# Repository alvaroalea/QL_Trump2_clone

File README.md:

# SINCLAIR QL Trump Card V2 disk interface

(C) 2022 Alvaro Alea Fernandez

License under: CERN Open Hardware Licence Version 2 - Strongly Reciprocal

https://ohwr.org/cern_ohl_s_v2.txt

Available in the market in 4 ways, 0K, 256Kb/ACE, 512Kb, 768Kb and Treo (256Kb aditional).

Only 0Kb has been tested.

Check the readme in the GAL folder, up to now, I only be able to make it work without RAM.

# Technical Info

## Components to use

### 4040
We found that not all manufacturer made CD4040 or 74HC4040 in the same way, and some made counter with rise-edge of clock, and some with falling-edge.

The trump card need falling edge or will mess with the refresh cycle and do not work.

The eprom/gal programer TL-866 II+ has a function to test TLL chips, but fail to detect it and consider valid both variants.

We have include the file 4040-test.lgc with a custom test that when load on the programmer allow to detect valid 74HC4040 variants. (best to use 74HC4040 that CD4040)

### RAM Chips
Trump Card use 514256 Ram chips, this is 4bits x 256K (1Mbit) Dinamic RAM.

Trump Card use a special refresh mode of this chips called hidden refresh, but not all manufacturer implement in tha same way.

Has been reported that Texas Instrument TMS44C256 are not valid and will cause errors on boot.

Motorola (MCM514256) Siemens (HYB514256) and OKI (MSM514256) has been reported to work

Toshiba (TC514256) and GoldStart (GM71C4256) al also valid acording to datasheet, but not tested.

The trump card schematic used 0 wait state ram, even in the refresh cycle, and for that speed of the dram shall be between 70 and 100ns, 120ns or slower are not valid.

HOLD

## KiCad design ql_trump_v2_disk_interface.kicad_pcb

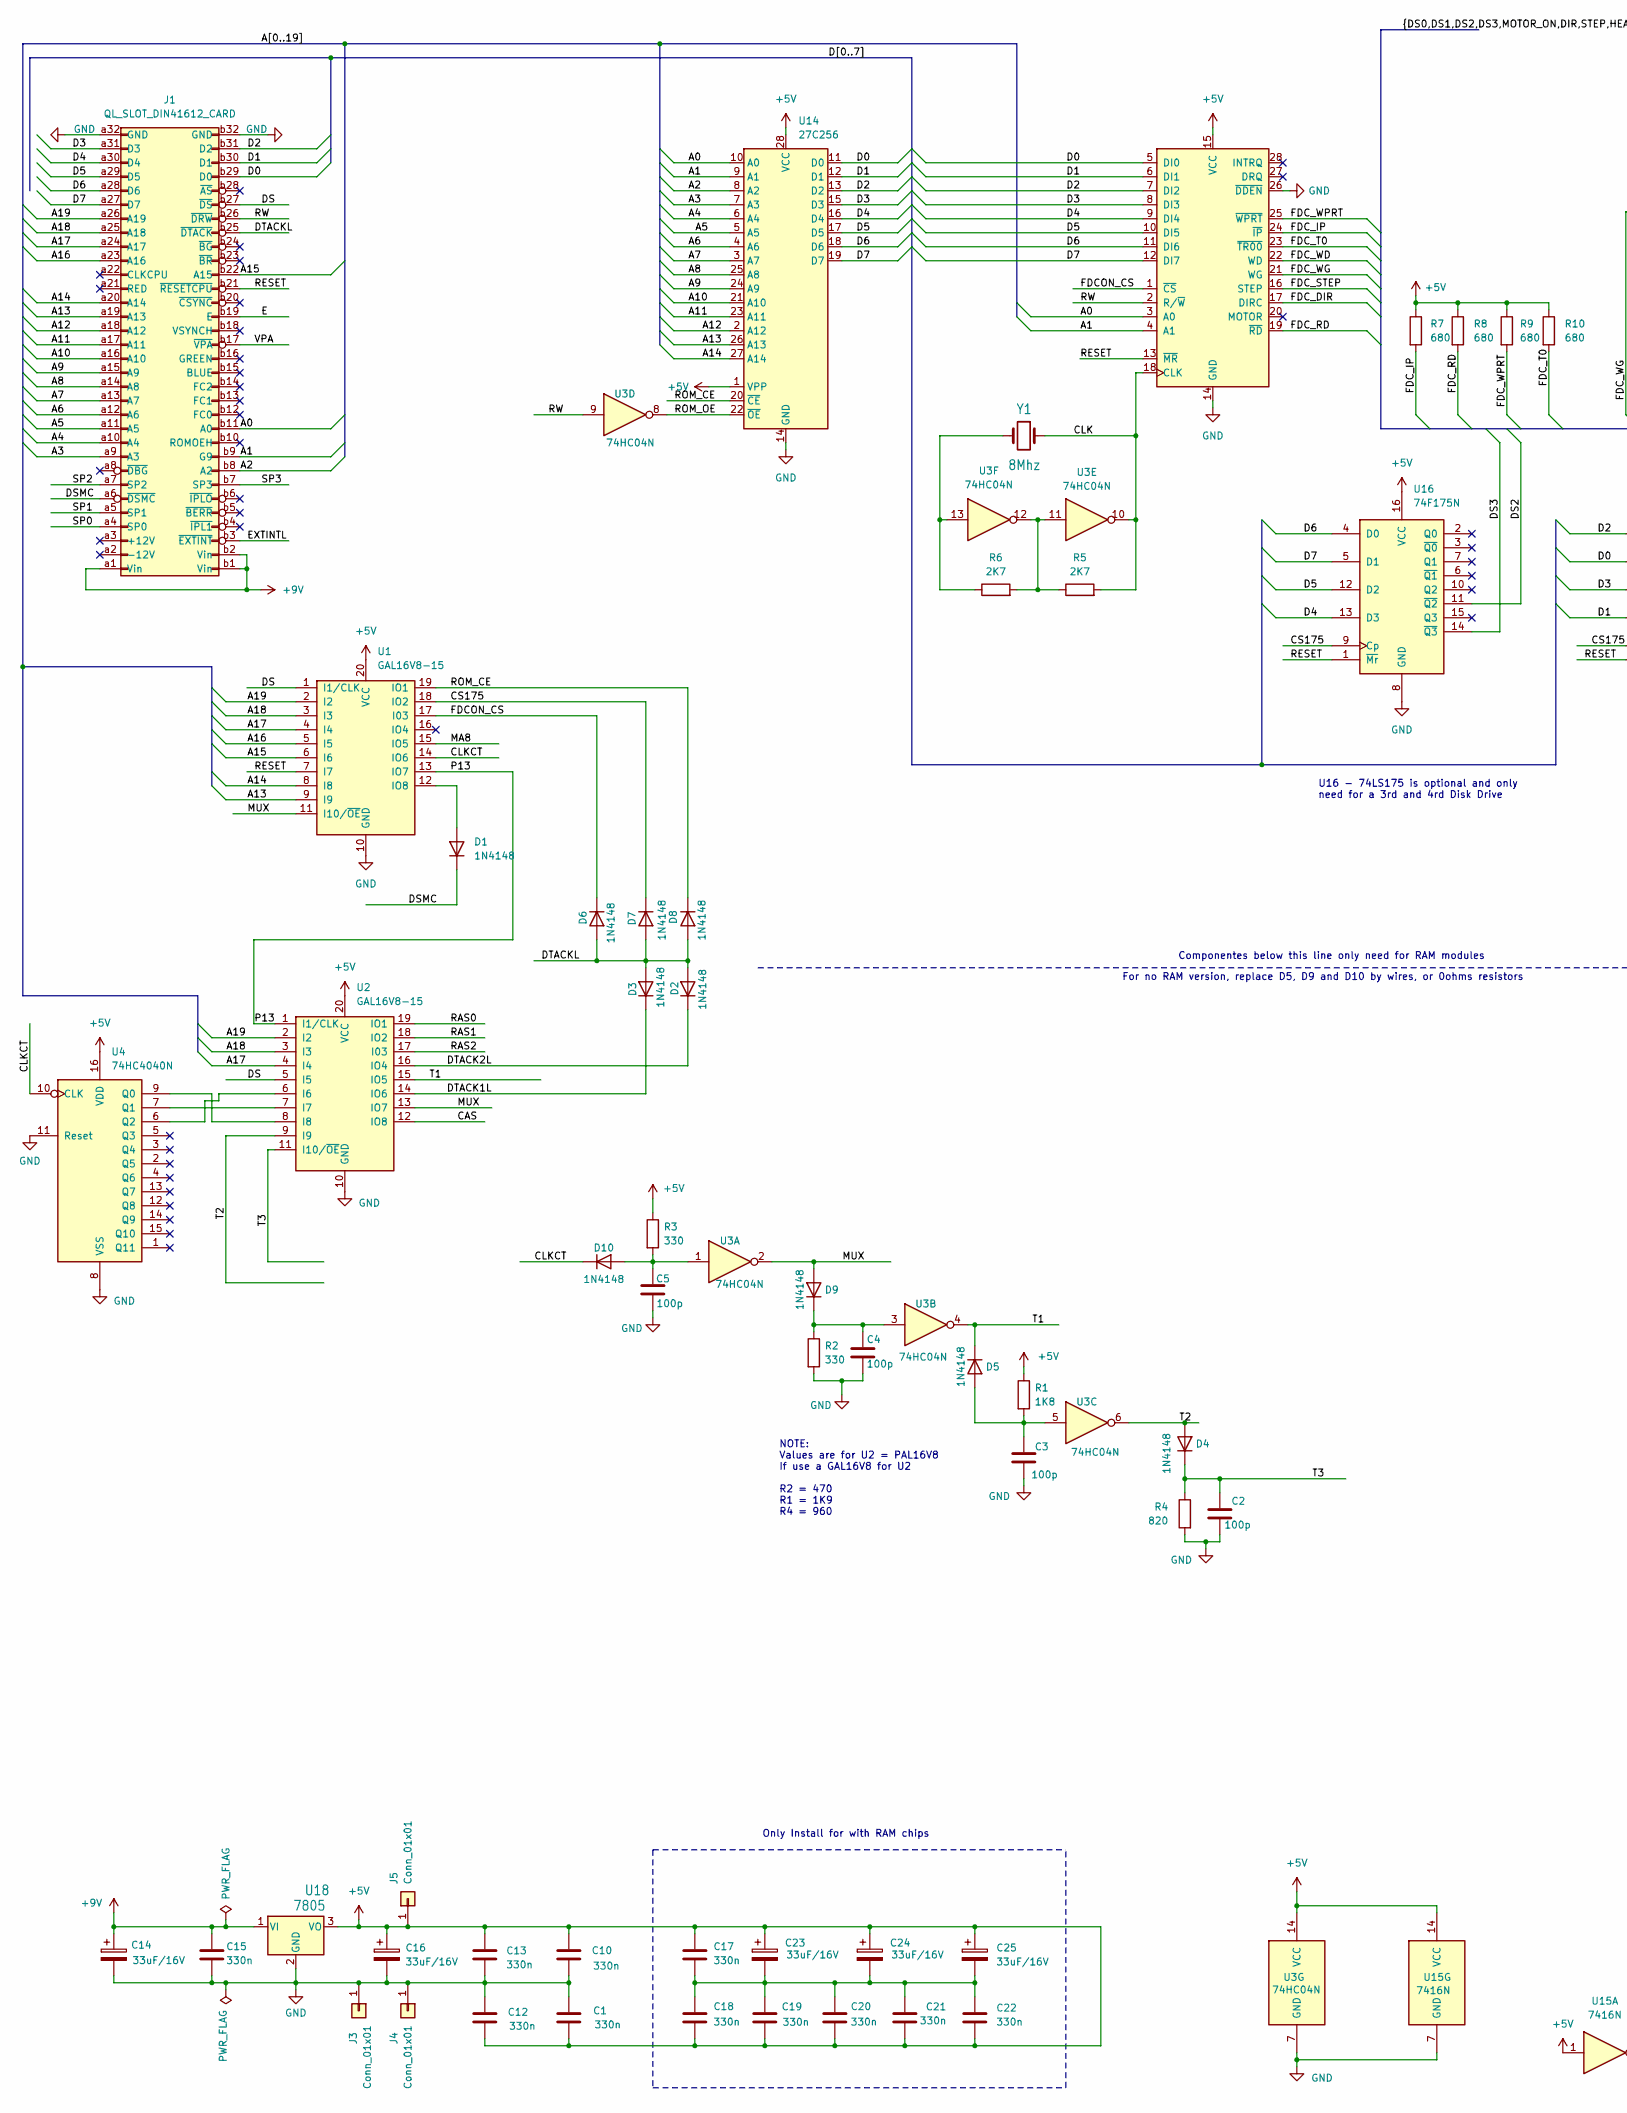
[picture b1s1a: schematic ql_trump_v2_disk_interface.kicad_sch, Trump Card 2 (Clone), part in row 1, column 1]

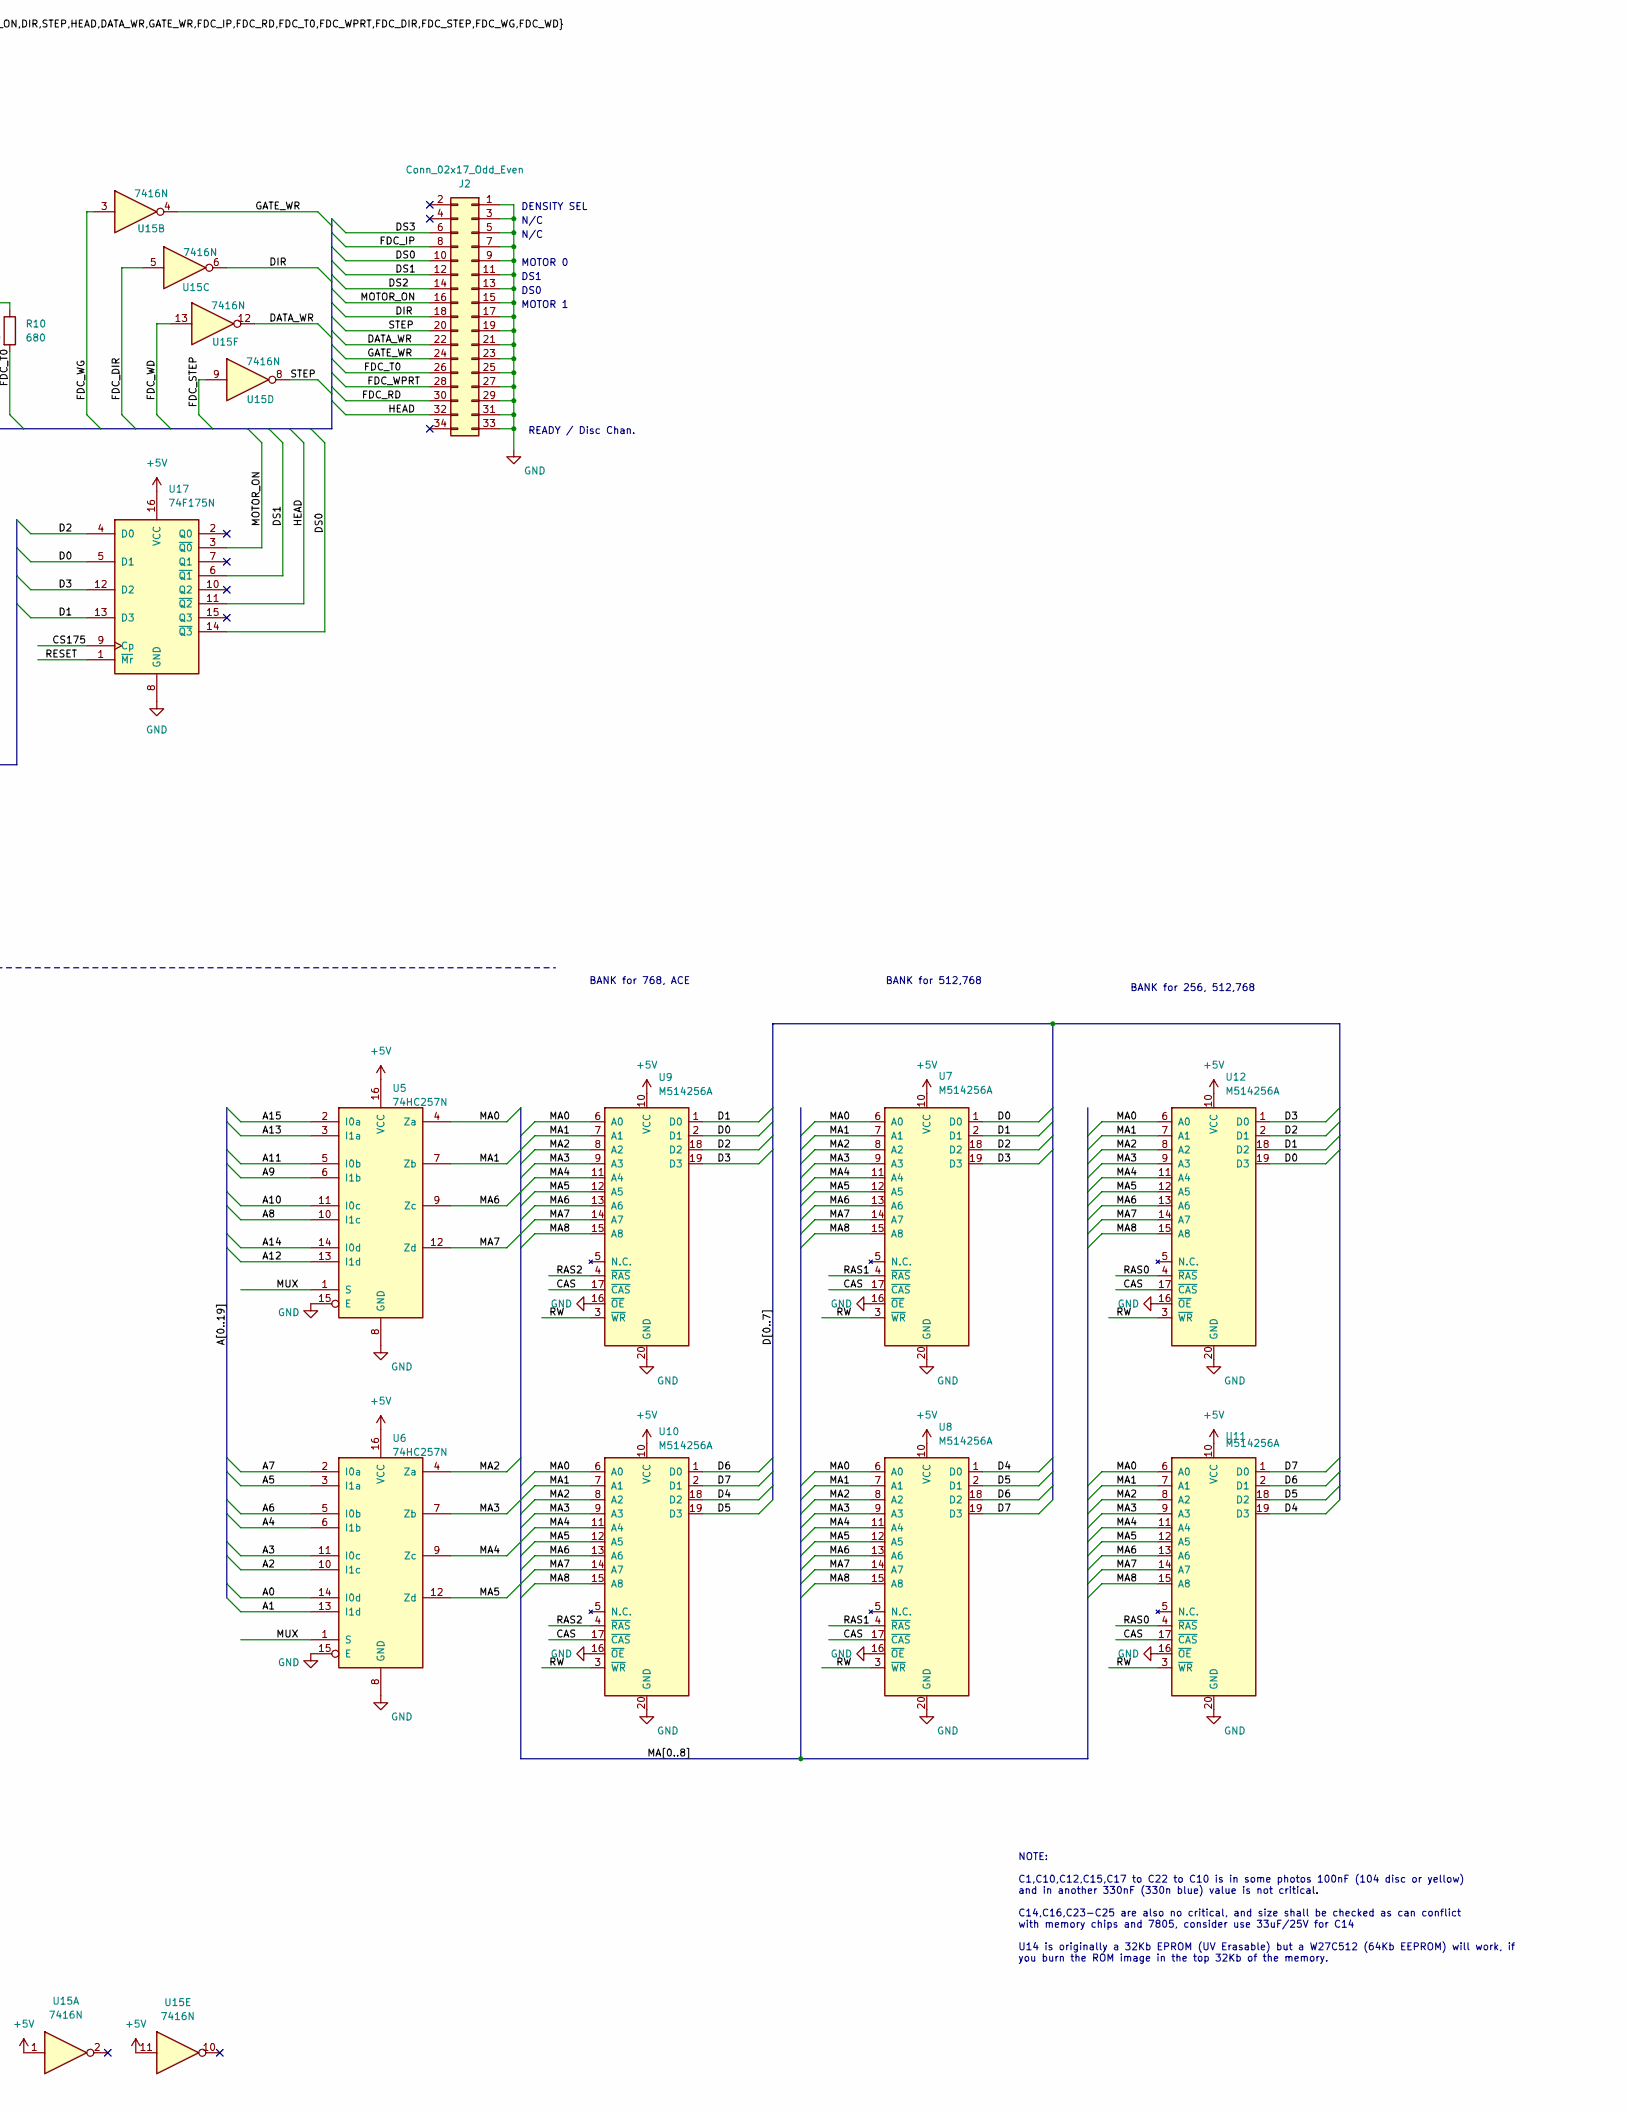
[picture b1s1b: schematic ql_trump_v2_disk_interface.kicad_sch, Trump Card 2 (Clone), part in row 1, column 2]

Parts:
C1, C10, C12, C17, C18, C19, C20, C21, C22: 330n; C_Disc_D7.5mm_W4.4mm_P5.00mm
C2, C3, C4, C5: 100p; C_Disc_D7.0mm_W2.5mm_P5.00mm
C13, C15: 330n; C_Disc_D5.1mm_W3.2mm_P5.00mm
C14, C16, C23, C24, C25: 33uF/16V; CP_Axial_L11.0mm_D5.0mm_P18.00mm_Horizontal
D1, D2, D3, D4, D5, D6, D7, D8, D9, D10: 1N4148; D_DO-35_SOD27_P10.16mm_Horizontal
J1: QL_SLOT_DIN41612_CARD; DIN41612_Q_2x32_Female_Horizontal_THT
J2: Conn_02x17_Odd_Even; PinHeader_2x17_P2.54mm_Horizontal
J3, J4, J5: Conn_01x01; TestPoint_THTPad_D1.5mm_Drill0.7mm
R1: 1K8; R_Axial_DIN0207_L6.3mm_D2.5mm_P10.16mm_Horizontal
R2, R3: 330; R_Axial_DIN0207_L6.3mm_D2.5mm_P10.16mm_Horizontal
R4: 820; R_Axial_DIN0207_L6.3mm_D2.5mm_P10.16mm_Horizontal
R5, R6: 2K7; R_Axial_DIN0207_L6.3mm_D2.5mm_P10.16mm_Horizontal
R7, R8, R9, R10: 680; R_Axial_DIN0207_L6.3mm_D2.5mm_P10.16mm_Horizontal
U1, U2: GAL16V8-15; DIP-20_W7.62mm
U3: 74HC04N; DIP-14_W7.62mm
U4: 74HC4040N; DIP-16_W7.62mm
U5, U6: 74HC257N; DIP-16_W7.62mm
U7, U8, U9, U10, U11, U12: M514256A; DIP-20_W7.62mm
U13: FDC_WD1772; DIP-28_W15.24mm
U14: 27C256; DIP-28_W15.24mm
U15: 7416N; DIP-14_W7.62mm
U16, U17: 74F175N; DIP-16_W7.62mm
U18: 7805; TO-220-3_Horizontal_TabDown
Y1: 8Mhz; Crystal_HC18-U_Vertical

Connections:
+5V: C1.1, C10.2, C12.1, C13.1, C16.1, C17.1, C18.1, C19.2, C20.1, C21.2, C22.1, C23.1, C24.1, C25.1, J5.1, R1.1, R3.1, R7.1, R8.1, R9.1, R10.1, U1.20 (VCC), U2.20 (VCC), U3.14 (VCC), U4.16 (VDD), U5.16 (VCC), U6.16 (VCC), U7.10 (VCC), U8.10 (VCC), U9.10 (VCC), U10.10 (VCC), U11.10 (VCC), U12.10 (VCC), U13.15 (VCC), U14.1 (VPP), U14.28 (VCC), U15.1, U15.11, U15.14 (VCC), U16.16 (VCC), U17.16 (VCC), U18.3 (VO)
+9V: C14.1, C15.1, J1.a1 (Vin), J1.b1 (Vin), J1.b2 (Vin), U18.1 (VI)
/A0: J1.b11 (A0), U6.14 (I0d), U13.3 (A0), U14.10 (A0)
/A1: J1.b9 (G9), U6.13 (I1d), U13.4 (A1), U14.9 (A1)
/A2: J1.b8 (A2), U6.10 (I1c), U14.8 (A2)
/A3: J1.a9 (A3), U6.11 (I0c), U14.7 (A3)
/A4: J1.a10 (A4), U6.6 (I1b), U14.6 (A4)
/A5: J1.a11 (A5), U6.3 (I1a), U14.5 (A5)
/A6: J1.a12 (A6), U6.5 (I0b), U14.4 (A6)
/A7: J1.a13 (A7), U6.2 (I0a), U14.3 (A7)
/A8: J1.a14 (A8), U5.10 (I1c), U14.25 (A8)
/A9: J1.a15 (A9), U5.6 (I1b), U14.24 (A9)
/A10: J1.a16 (A10), U5.11 (I0c), U14.21 (A10)
/A11: J1.a17 (A11), U5.5 (I0b), U14.23 (A11)
/A12: J1.a18 (A12), U5.13 (I1d), U14.2 (A12)
/A13: J1.a19 (A13), U1.9 (I9), U5.3 (I1a), U14.26 (A13)
/A14: J1.a20 (A14), U1.8 (I8), U5.14 (I0d), U14.27 (A14)
/A15: J1.b22 (A15), U1.6 (I6), U5.2 (I0a)
/A16: J1.a23 (A16), U1.5 (I5)
/A17: J1.a24 (A17), U1.4 (I4), U2.4 (I4)
/A18: J1.a25 (A18), U1.3 (I3), U2.3 (I3)
/A19: J1.a26 (A19), U1.2 (I2), U2.2 (I2)
/CAS: U2.12 (IO8), U7.17 (~CAS), U8.17 (~CAS), U9.17 (~CAS), U10.17 (~CAS), U11.17 (~CAS), U12.17 (~CAS)
/CLK: R5.2, U3.10, U13.18 (CLK), Y1.1
/CLKCT: D10.1 (K), U1.14 (IO6), U4.10 (CLK)
/CS175: D7.1 (K), U1.18 (IO2), U16.9 (Cp), U17.9 (Cp)
/D0: J1.b29 (D0), U7.1 (D0), U9.2 (D1), U12.19 (D3), U13.5 (DI0), U14.11 (D0), U17.5 (D1)
/D1: J1.b30 (D1), U7.2 (D1), U9.1 (D0), U12.18 (D2), U13.6 (DI1), U14.12 (D1), U17.13 (D3)
/D2: J1.b31 (D2), U7.18 (D2), U9.18 (D2), U12.2 (D1), U13.7 (DI2), U14.13 (D2), U17.4 (D0)
/D3: J1.a31 (D3), U7.19 (D3), U9.19 (D3), U12.1 (D0), U13.8 (DI3), U14.15 (D3), U17.12 (D2)
/D4: J1.a30 (D4), U8.1 (D0), U10.18 (D2), U11.19 (D3), U13.9 (DI4), U14.16 (D4), U16.13 (D3)
/D5: J1.a29 (D5), U8.2 (D1), U10.19 (D3), U11.18 (D2), U13.10 (DI5), U14.17 (D5), U16.12 (D2)
/D6: J1.a28 (D6), U8.18 (D2), U10.1 (D0), U11.2 (D1), U13.11 (DI6), U14.18 (D6), U16.4 (D0)
/D7: J1.a27 (D7), U8.19 (D3), U10.2 (D1), U11.1 (D0), U13.12 (DI7), U14.19 (D7), U16.5 (D1)
/DATA_WR: J2.22, U15.12
/DIR: J2.18, U15.6
/DS: J1.b27 (~DS), U1.1 (I1/CLK), U2.5 (I5)
/DS0: J2.10, U17.14 (~Q3)
/DS1: J2.12, U17.6 (~Q1)
/DS2: J2.14, U16.11 (~Q2)
/DS3: J2.6, U16.14 (~Q3)
/DSMC: D1.1 (K), J1.a6 (~DSMC)
/DTACK1L: D3.1 (K), U2.14 (IO6)
/DTACK2L: D2.1 (K), U2.16 (IO4)
/DTACKL: D2.2 (A), D3.2 (A), D6.2 (A), D7.2 (A), D8.2 (A), J1.b25 (~DTACK)
/E: J1.b19 (E)
/EXTINTL: J1.b3 (~EXTINT)
/FDCON_CS: D6.1 (K), U1.17 (I03), U13.1 (~CS)
/FDC_DIR: U13.17 (DIRC), U15.5
/FDC_IP: J2.8, R7.2, U13.24 (~IP)
/FDC_RD: J2.30, R8.2, U13.19 (~RD)
/FDC_STEP: U13.16 (STEP), U15.9
/FDC_T0: J2.26, R10.2, U13.23 (~TR00)
/FDC_WD: U13.22 (WD), U15.13
/FDC_WG: U13.21 (WG), U15.3
/FDC_WPRT: J2.28, R9.2, U13.25 (~WPRT)
/GATE_WR: J2.24, U15.4
/HEAD: J2.32, U17.11 (~Q2)
/MA0: U5.4 (Za), U7.6 (A0), U8.6 (A0), U9.6 (A0), U10.6 (A0), U11.6 (A0), U12.6 (A0)
/MA1: U5.7 (Zb), U7.7 (A1), U8.7 (A1), U9.7 (A1), U10.7 (A1), U11.7 (A1), U12.7 (A1)
/MA2: U6.4 (Za), U7.8 (A2), U8.8 (A2), U9.8 (A2), U10.8 (A2), U11.8 (A2), U12.8 (A2)
/MA3: U6.7 (Zb), U7.9 (A3), U8.9 (A3), U9.9 (A3), U10.9 (A3), U11.9 (A3), U12.9 (A3)
/MA4: U6.9 (Zc), U7.11 (A4), U8.11 (A4), U9.11 (A4), U10.11 (A4), U11.11 (A4), U12.11 (A4)
/MA5: U6.12 (Zd), U7.12 (A5), U8.12 (A5), U9.12 (A5), U10.12 (A5), U11.12 (A5), U12.12 (A5)
/MA6: U5.9 (Zc), U7.13 (A6), U8.13 (A6), U9.13 (A6), U10.13 (A6), U11.13 (A6), U12.13 (A6)
/MA7: U5.12 (Zd), U7.14 (A7), U8.14 (A7), U9.14 (A7), U10.14 (A7), U11.14 (A7), U12.14 (A7)
/MA8: U1.15 (IO5), U7.15 (A8), U8.15 (A8), U9.15 (A8), U10.15 (A8), U11.15 (A8), U12.15 (A8)
/MOTOR_ON: J2.16, U17.3 (~Q0)
/MUX: D9.2 (A), U1.11 (I10/~OE), U2.13 (IO7), U3.2, U5.1 (S), U6.1 (S)
/P13: U1.13 (IO7), U2.1 (I1/CLK)
/RAS0: U2.19 (IO1), U11.4 (~RAS), U12.4 (~RAS)
/RAS1: U2.18 (IO2), U7.4 (~RAS), U8.4 (~RAS)
/RAS2: U2.17 (I03), U9.4 (~RAS), U10.4 (~RAS)
/RESET: J1.b21 (~RESETCPU), U1.7 (I7), U13.13 (~MR), U16.1 (~Mr), U17.1 (~Mr)
/ROM_CE: D8.1 (K), U1.19 (IO1), U14.20 (~CE)
/ROM_OE: U3.8, U14.22 (~OE)
/RW: J1.b26 (~DRW), U3.9, U7.3 (~WR), U8.3 (~WR), U9.3 (~WR), U10.3 (~WR), U11.3 (~WR), U12.3 (~WR), U13.2 (R/~W)
/SP0: J1.a4 (SP0)
/SP1: J1.a5 (SP1)
/SP2: J1.a7 (SP2)
/SP3: J1.b7 (SP3)
/STEP: J2.20, U15.8
/T1: D5.1 (K), U2.15 (IO5), U3.4
/T2: D4.2 (A), U2.9 (I9), U3.6
/T3: C2.2, D4.1 (K), R4.1, U2.11 (I10/~OE)
/VPA: J1.b17 (~VPA)
unnamed: D1.2 (A), U1.12 (IO8)
unnamed: C3.1, D5.2 (A), R1.2, U3.5
unnamed: C4.2, D9.1 (K), R2.1, U3.3
unnamed: C5.1, D10.2 (A), R3.2, U3.1
unnamed: R5.1, R6.2, U3.11, U3.12
unnamed: R6.1, U3.13, Y1.2
unnamed: U2.6 (I6), U4.6 (Q2)
unnamed: U2.7 (I7), U4.7 (Q1)
unnamed: U2.8 (I8), U4.9 (Q0)

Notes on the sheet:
NOTE: C1,C10,C12,C15,C17 to C22 to C10 is in some photos 100nF (104 disc or yellow) and in another 330nF (330n blue) value is not critical. C14,C16,C23-C25 are also no critical, and size shall be checked as can conflict with memory chips and 7805, consider use 33uF/25V for C14 U14 is originally a 3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
MOTOR 0
BANK for 512,768
DS0
DS1
READY / Disc Chan.
MOTOR 1
U16 - 74LS175 is optional and only need for a 3rd and 4rd Disk Drive
For no RAM version, replace D5, D9 and D10 by wires, or 0ohms resistors
Componentes below this line only need for RAM modules
N/C
Only Install for with RAM chips
BANK for 768, ACE
NOTE: Values are for U2 = PAL16V8 If use a GAL16V8 for U2 R2 = 470 R1 = 1K9 R4 = 960
DENSITY SEL
BANK for 256, 512,768

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
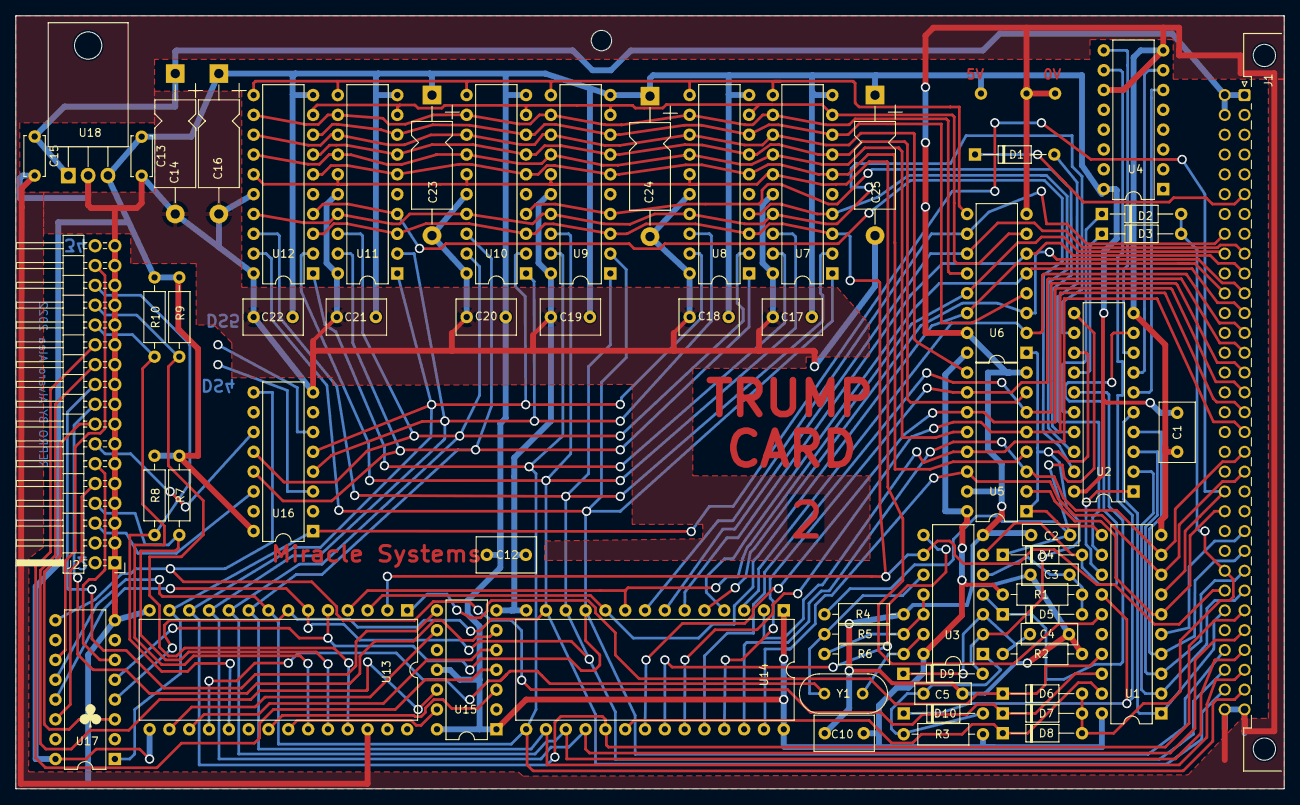
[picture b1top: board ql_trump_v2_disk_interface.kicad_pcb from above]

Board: 2 copper layers, 162.6 x 99.1 mm, 64 parts (0 on the bottom side), 89 nets.

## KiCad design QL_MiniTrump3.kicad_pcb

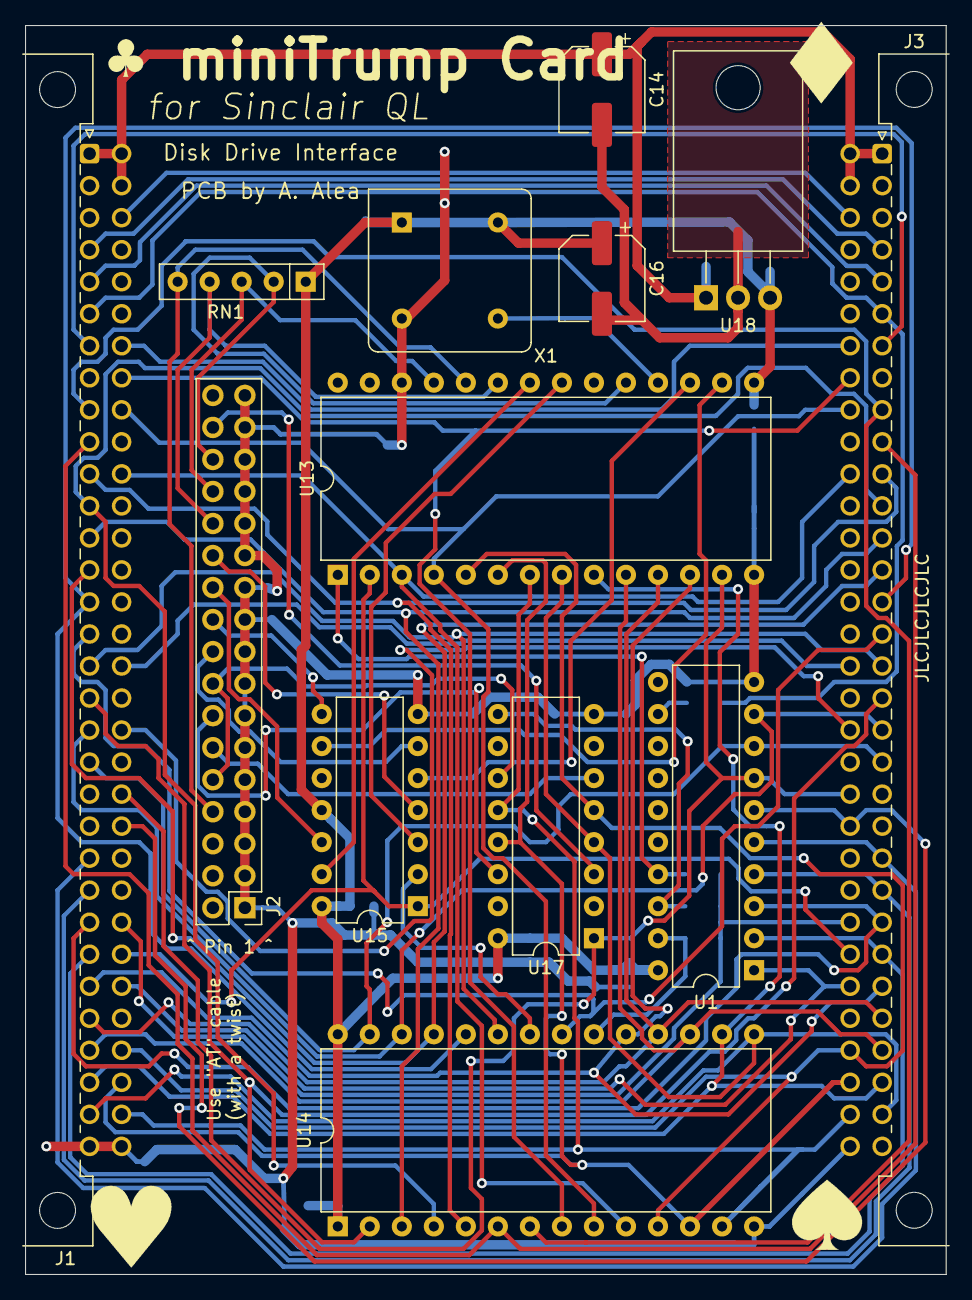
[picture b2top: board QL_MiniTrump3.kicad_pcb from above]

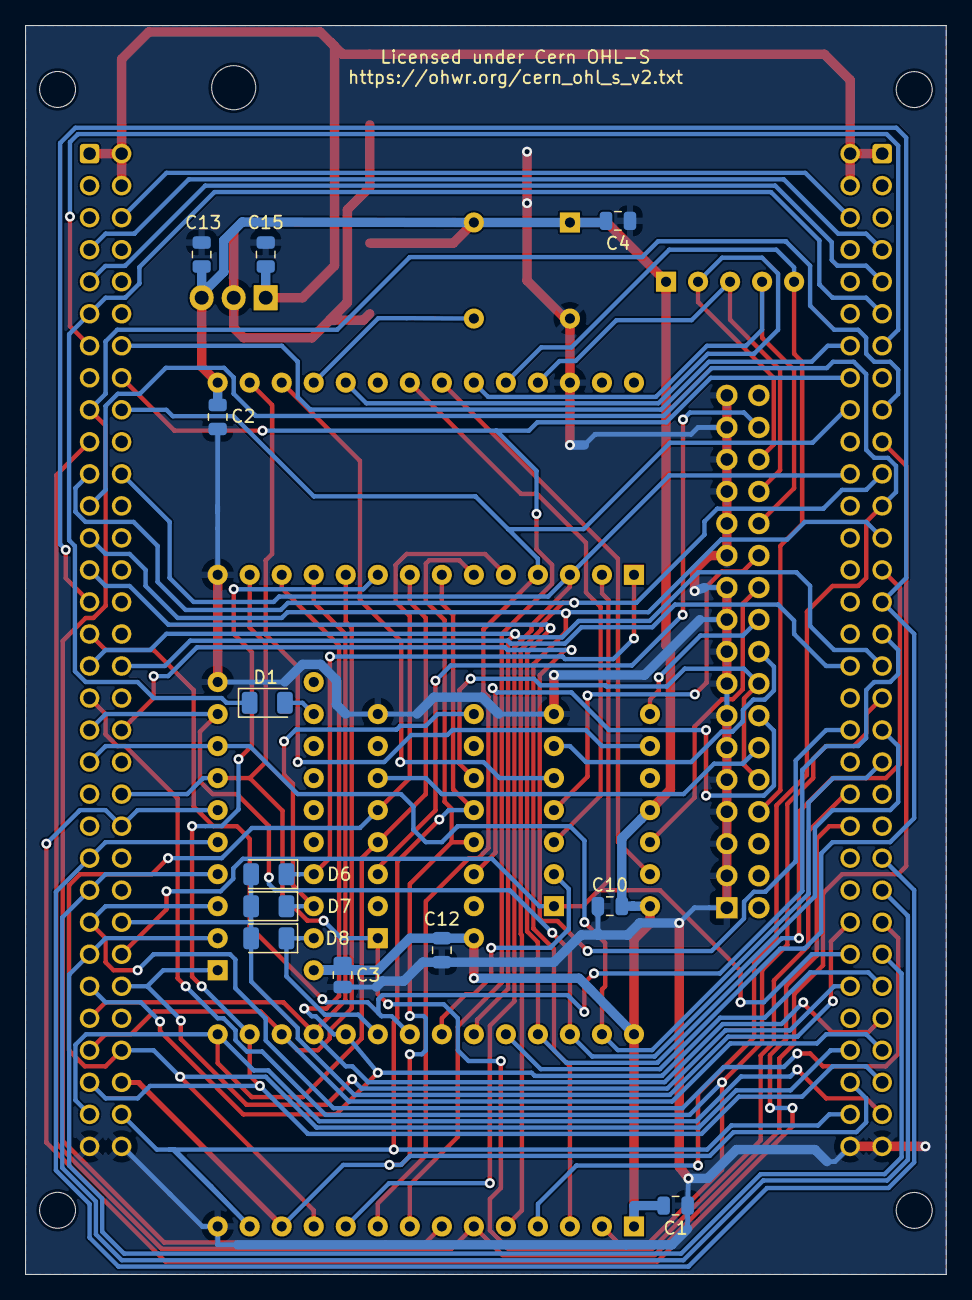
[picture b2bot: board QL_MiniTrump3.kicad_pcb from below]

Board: 2 copper layers, 73.0 x 99.1 mm, 25 parts (12 on the bottom side), 65 nets.

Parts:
C1, C2, C3, C4, C10, C12, C13, C15: C; C_0805_2012Metric
C14, C16: C_Polarized; CP_Elec_6.3x5.4
D1, D6, D7, D8: 1N4148; D_1206_3216Metric
J1: QL_SLOT_DIN41612_CARD; DIN41612_B_2x32_Female_Horizontal_THT
J2: Conn_02x17_Odd_Even; PinHeader_2x17_P2.54mm_Vertical
J3: QL_SLOT_DIN41612_CARD; DIN41612_B_2x32_Male_Horizontal_THT
RN1: 4x680; R_Array_SIP5
U: FDC_WD1772; DIP-28_W15.24mm
U1: GAL16V8; DIP-20_W7.62mm
U14: 27C128; DIP-28_W15.24mm
U15: 74HC04; DIP-14_W7.62mm
U17: 74ls175; DIP-16_W7.62mm
U18: 7805; TO-220-3_Horizontal_TabDown
X1: CXO_DIP8; Oscillator_DIP-8

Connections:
+5V: C1.1, C2.2, C3.2, C4.2, C10.2, C12.1, C13.1, C16.1, RN1.1 (common), U.15 (VCC), U1.20 (VCC), U14.1 (VPP), U14.28 (VCC), U15.11, U15.14 (VCC), U17.16 (VCC), U18.3 (VO), X1.1 (EN), X1.8 (Vcc)
+9V: C14.1, C15.1, J1.a1 (Vin), J1.b1 (Vin), J1.b2 (Vin), J3.a1 (Vin), J3.b1 (Vin), J3.b2 (Vin), U18.1 (VI)
/A0: J1.b11 (A0), J3.b11 (A0), U.3 (A0), U14.10 (A0)
/A1: J1.b9 (G9), J3.b9 (G9), U.4 (A1), U14.9 (A1)
/A2: J1.b8 (A2), J3.b8 (A2), U14.8 (A2)
/A3: J1.a9 (A3), J3.a9 (A3), U14.7 (A3)
/A4: J1.a10 (A4), J3.a10 (A4), U14.6 (A4)
/A5: J1.a11 (A5), J3.a11 (A5), U14.5 (A5)
/A6: J1.a12 (A6), J3.a12 (A6), U14.4 (A6)
/A7: J1.a13 (A7), J3.a13 (A7), U14.3 (A7)
/A8: J1.a14 (A8), J3.a14 (A8), U14.25 (A8)
/A9: J1.a15 (A9), J3.a15 (A9), U14.24 (A9)
/A10: J1.a16 (A10), J3.a16 (A10), U14.21 (A10)
/A11: J1.a17 (A11), J3.a17 (A11), U14.23 (A11)
/A12: J1.a18 (A12), J3.a18 (A12), U14.2 (A12)
/A13: J1.a19 (A13), J3.a19 (A13), U1.9 (I9), U14.26 (A13)
/A14: J1.a20 (A14), J3.a20 (A14), U1.8 (I8), U14.27 (A14)
/A15: J1.b22 (A15), J3.b22 (A15), U1.6 (I6)
/A16: J1.a23 (A16), J3.a23 (A16), U1.5 (I5)
/A17: J1.a24 (A17), J3.a24 (A17), U1.4 (I4)
/A18: J1.a25 (A18), J3.a25 (A18), U1.3 (I3)
/A19: J1.a26 (A19), J3.a26 (A19), U1.2 (I2)
/CS175: D7.1 (K), U1.18 (IO2), U17.9 (Cp)
/D0: J1.b29 (D0), J3.b29 (D0), U.5 (DI0), U14.11 (D0), U17.5 (D1)
/D1: J1.b30 (D1), J3.b30 (D1), U.6 (DI1), U14.12 (D1), U17.13 (D3)
/D2: J1.b31 (D2), J3.b31 (D2), U.7 (DI2), U14.13 (D2), U17.12 (D2)
/D3: J1.a31 (D3), J3.a31 (D3), U.8 (DI3), U14.15 (D3), U17.4 (D0)
/D4: J1.a30 (D4), J3.a30 (D4), U.9 (DI4), U14.16 (D4)
/D5: J1.a29 (D5), J3.a29 (D5), U.10 (DI5), U14.17 (D5)
/D6: J1.a28 (D6), J3.a28 (D6), U.11 (DI6), U14.18 (D6)
/D7: J1.a27 (D7), J3.a27 (D7), U.12 (DI7), U14.19 (D7)
/DATA_WR: J2.22, U15.12
/DIR: J2.18, U15.6
/DS: J1.b27 (~DS), J3.b27 (~DS), U1.1 (I1/CLK)
/DS0: J2.14, U17.14 (~Q3)
/DS1: J2.12, U17.6 (~Q1)
/DSMC: D1.1 (K), J1.a6 (~DSMC), J3.a6 (~DSMC)
/DTACKL: D6.2 (A), D7.2 (A), D8.2 (A), J1.b25 (~DTACK), J3.b25 (~DTACK)
/E: J1.b19 (E), J3.b19 (E)
/EXTINTL: J1.b3 (~EXTINT), J3.b3 (~EXTINT)
/FDCON_CS: D6.1 (K), U.1 (~CS), U1.17 (I03)
/FDC_DIR: U.17 (DIRC), U15.5
/FDC_IP: J2.8, RN1.5 (R4), U.24 (~IP)
/FDC_RD: J2.30, RN1.2 (R1), U.19 (~RD)
/FDC_STEP: U.16 (STEP), U15.9
/FDC_T0: J2.26, RN1.4 (R3), U.23 (~TR00)
/FDC_WD: U.22 (WD), U15.13
/FDC_WG: U.21 (WG), U15.3
/FDC_WPRT: J2.28, RN1.3 (R2), U.25 (~WPRT)
/GATE_WR: J2.24, U15.4
/HEAD: J2.32, U17.3 (~Q0)
/MOTOR_ON: J2.10, J2.16, U17.11 (~Q2)
/RESET: J1.b21 (~RESETCPU), J3.b21 (~RESETCPU), U.13 (~MR), U1.7 (I7), U17.1 (~Mr)
/ROM_CE: D8.1 (K), U1.19 (IO1), U14.20 (~CE)
/ROM_OE: U14.22 (~OE), U15.2
/RW: J1.b26 (~DRW), J3.b26 (~DRW), U.2 (R/~W), U15.1
/SP0: J1.a4 (SP0), J3.a4 (SP0)
/SP1: J1.a5 (SP1), J3.a5 (SP1)
/SP2: J1.a7 (SP2), J3.a7 (SP2)
/SP3: J1.b7 (SP3), J3.b7 (SP3)
/STEP: J2.20, U15.8
/VPA: J1.b17 (~VPA), J3.b17 (~VPA)
GND: C1.2, C2.1, C3.1, C4.1, C10.1, C12.2, C13.2, C14.2, C15.2, C16.2, J1.a32 (GND), J1.b32 (GND), J2.1, J2.3, J2.5, J2.7, J2.9, J2.11, J2.13, J2.15, J2.17, J2.19, J2.21, J2.23, J2.25, J2.27, J2.29, J2.31, J2.33, J3.a32 (GND), J3.b32 (GND), U.14 (GND), U.26 (~DDEN), U1.10 (GND), U14.14 (GND), U15.7 (GND), U17.8 (GND), U18.2 (GND), X1.4 (GND)
unnamed: D1.2 (A), U1.12 (IO8)
unnamed: U.18 (CLK), X1.5 (OUT)

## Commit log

2022-10-01 ínicial
2022-10-01 more files
2024-05-07 Initial
2024-05-08 solucionada chapuza
2024-07-26 update BOM and gervers
2024-08-13 fix ROM reference
2024-11-11 some updated on GALs
2024-11-22 minor typos
2025-06-10 update related to GAL chips
2025-06-14 internal changes on GAL
2025-06-14 add comments to GAL source
2025-06-15 update gal info
2025-06-15 new datasheet for TI memory
2025-07-19 more graphics
2025-08-03 included information of IC
2025-12-16 new devel branch
2026-02-28 small details
2026-02-28 add plate

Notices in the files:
QL_MiniTrump3.kicad_pcb:
Licensed under Cern OHL-S
